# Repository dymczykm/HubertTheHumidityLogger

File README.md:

# Hubert the Humidity Logger

Huber the Humidity Logger is a project of an IoT device that measures the relative humidity, temperature and pressure and reports it back to a remote server using the built-in 4G modem. I created this project as I couldn't find a device off the shelf that could log humidity using the cellular network and would not cost an arm and a leg.

Hubert can use a HTTP POST action to submit data to virtually any server, either running in the cloud (I tested it with https://io.adafruit.com/) or maintained on your own (my Hubert is submitting data to a Raspberry Pi running InfluxDB).

Hubert is build around (Makerfabs Maduino Zero 4G LTE)[ttps://www.makerfabs.com/maduino-zero-4g-lte-sim7600.html] and loosely inspired by the [DIY Life 4G air quality weather station](https://www.the-diy-life.com/diy-4g-air-quality-and-environment-monitor-record-data-anywhere/).

For more details, please refer to the project page: https://dymczyk.com/hubert-the-humidity-logger

## Hardware

To build Hubert, you need the following components:
- Maduino Zero 4G/LTE board: https://www.makerfabs.com/maduino-zero-4g-lte-sim7600.html (includes an Arduino Zero compatible MCU + a Simcom 7600 modem)
- Hubert breakout board with a bunch of LEDs and a connector for the humidity sensor: KiCad files in `hardware/HumidityLoggerBreakout`
- BME280 sensor compatible with 3.3V supply [(Aliexpress item I used)](https://www.aliexpress.com/item/32862445164.html)
- A SIM card with some data allowance to post the humidity/temperature/pressure measurements

## Firmware

The firmware of Hubert is written in Arduino IDE and is located in `firmware/humidity_logger`.

The firmware does three main things:
1. Triggers the measurement process of BME280
2. POSTs the measurements to a remote server
3. Puts the modem and the MCU to sleep to save power

To adapt it to your application, you mostly need to put the credentials to access the server in `influxdb.h` file:
```
#define USER "xxx"
#define PASSWORD "xxx"
#define DB_URL "xxx"
```

## Remote server

Hubert uses a 4G connection to POST data to an InfluxDB database that resides on a remote server. In my case, it is a Raspberry Pi running continuously InfluxDB and Grafana to visualize the results in a nice dashboard.

## Case

I've designed a 3D printed case for Hubert, you can find the STL files for the top and the bottom in `hardware/case_stl`:

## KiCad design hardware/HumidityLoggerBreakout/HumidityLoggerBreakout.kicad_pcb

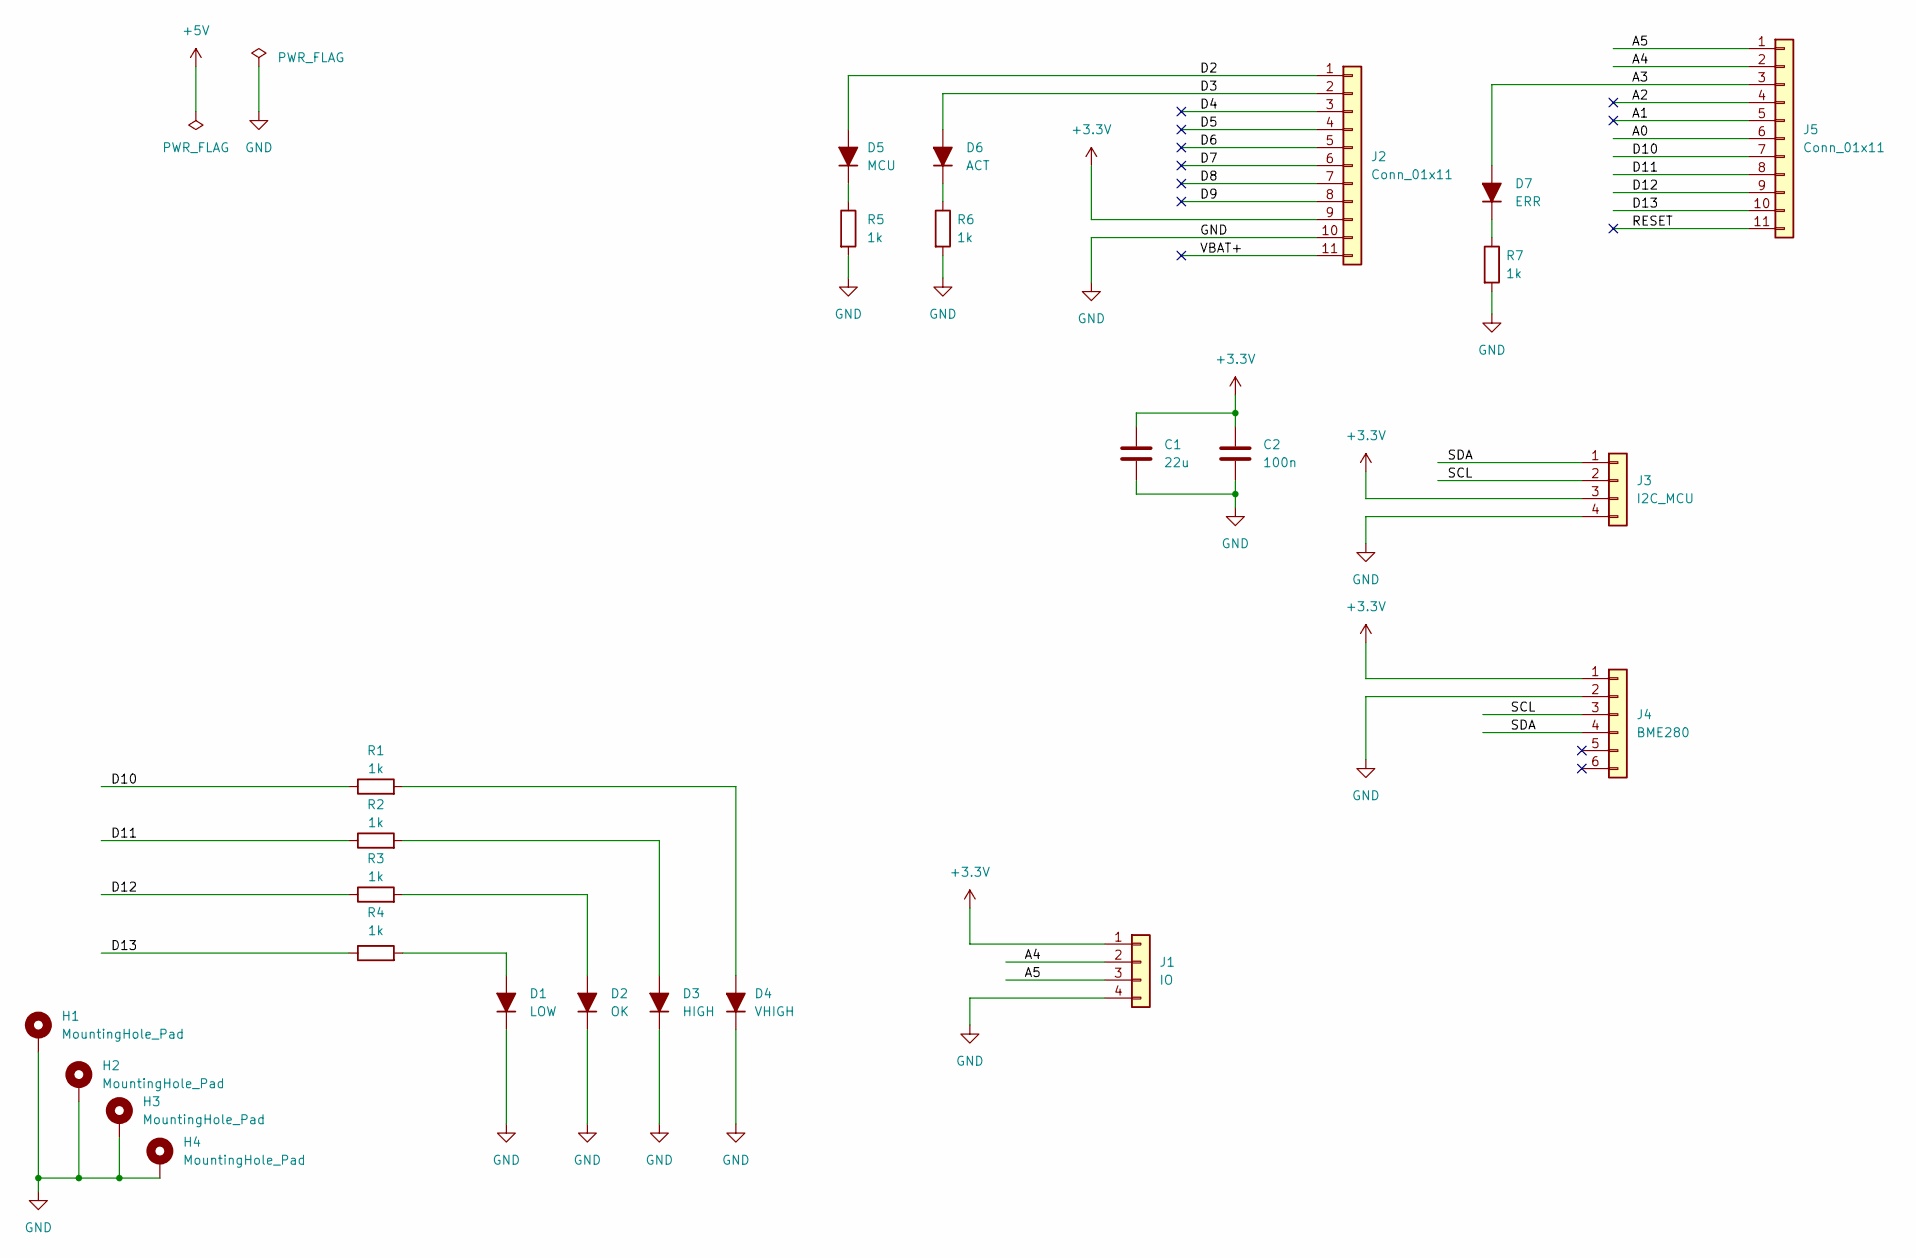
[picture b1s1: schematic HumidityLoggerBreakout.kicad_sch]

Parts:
C1: 22u; C_0805_2012Metric_Pad1.18x1.45mm_HandSolder; LCSC C45783
C2: 100n; C_0805_2012Metric_Pad1.18x1.45mm_HandSolder; LCSC C28233
D1: LOW; LED_0805_2012Metric_Pad1.15x1.40mm_HandSolder; LCSC C2297
D2: OK; LED_0805_2012Metric_Pad1.15x1.40mm_HandSolder; LCSC C2297
D3: HIGH; LED_0805_2012Metric_Pad1.15x1.40mm_HandSolder; LCSC C2297
D4: VHIGH; LED_0805_2012Metric_Pad1.15x1.40mm_HandSolder; LCSC C2297
D5: MCU; LED_0805_2012Metric_Pad1.15x1.40mm_HandSolder; LCSC C2297
D6: ACT; LED_0805_2012Metric_Pad1.15x1.40mm_HandSolder; LCSC C2296
D7: ERR; LED_0805_2012Metric_Pad1.15x1.40mm_HandSolder; LCSC C84256
H1, H2, H3, H4: MountingHole_Pad; MountingHole_2.7mm_M2.5_Pad_TopBottom
J1: IO; PinHeader_1x04_P2.54mm_Vertical
J2, J5: Conn_01x11; PinSocket_1x11_P2.54mm_Vertical
J3: I2C_MCU; PinSocket_1x04_P2.54mm_Vertical
J4: BME280; PinHeader_1x06_P2.54mm_Vertical
R1, R2, R3, R4, R5, R6, R7: 1k; R_0805_2012Metric_Pad1.20x1.40mm_HandSolder; LCSC C17513

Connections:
+3.3V: C1.1, C2.1, J1.1, J2.9, J3.3, J4.1
/A0: J5.6
/A1: J5.5
/A2: J5.4
/A3: D7.2 (A), J5.3
/A4: J1.2, J5.2
/A5: J1.3, J5.1
/D2: D5.2 (A), J2.1
/D3: D6.2 (A), J2.2
/D4: J2.3
/D5: J2.4
/D6: J2.5
/D7: J2.6
/D8: J2.7
/D9: J2.8
/D10: J5.7, R1.1
/D11: J5.8, R2.1
/D12: J5.9, R3.1
/D13: J5.10, R4.1
/RESET: J5.11
/SCL: J3.2, J4.3
/SDA: J3.1, J4.4
/VBAT+: J2.11
GND: C1.2, C2.2, D1.1 (K), D2.1 (K), D3.1 (K), D4.1 (K), H1.1, H2.1, H3.1, H4.1, J1.4, J2.10, J3.4, J4.2, R5.2, R6.2, R7.2
unnamed: D1.2 (A), R4.2
unnamed: D2.2 (A), R3.2
unnamed: D3.2 (A), R2.2
unnamed: D4.2 (A), R1.2
unnamed: D5.1 (K), R5.1
unnamed: D6.1 (K), R6.1
unnamed: D7.1 (K), R7.1

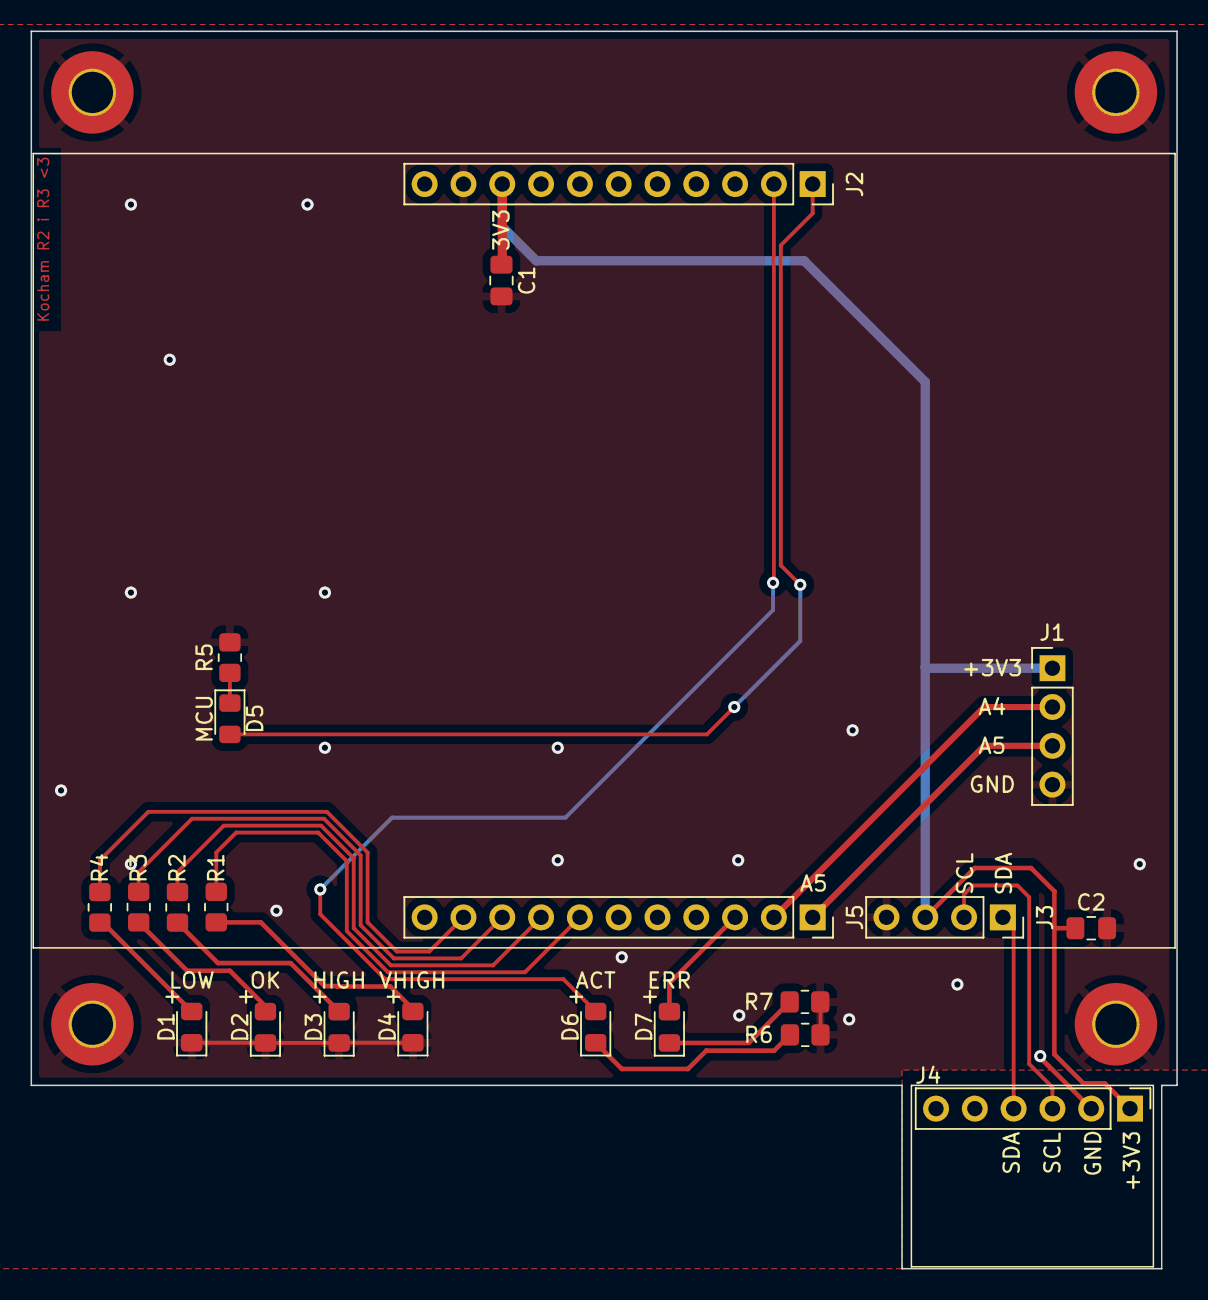
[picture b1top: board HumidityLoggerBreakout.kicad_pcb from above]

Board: 2 copper layers, 75.0 x 81.0 mm, 25 parts (0 on the bottom side), 20 nets.

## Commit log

2022-12-28 Working on the initial code.
2022-12-30 Fighting with POST.
2023-01-04 POST and GET work with Adafruit IO.
2023-01-05 Working on the SIM7600 routines.
2023-01-05 Cleanup of the http requests.
2023-01-05 Feed and pump control work.
2023-01-05 Some more cleanup.
2023-01-06 Added the breakout PCB for Maduino.
2023-01-06 First prototype production files.
2023-01-06 Minor corrections.
2023-01-19 The big connectors were flipped :(
2023-01-19 Fixed the connectors to Maduino.
2023-01-19 Minor.
2023-05-22 Modified the schematic to drop unnecessary features.
2023-05-26 WIP of the new version.
2023-05-30 WIP on the board.
2023-06-05 After updating the firmware USERDATA can be used again.
2023-06-05 Working with influxdb and grafana.
2023-06-10 Got the sensor and the LEDs to work.
2023-06-11 Added sleeping + LED blink.
2023-06-11 Works well, would like to add sleep for SIM7600 now.
2023-06-11 Added SIM7600 sleep.
2023-06-13 Red LED is blinking after the POST fails.
2023-06-21 RH LED test on boot.
2023-08-14 Restructure the dirs.
2023-08-14 Updated the README.
